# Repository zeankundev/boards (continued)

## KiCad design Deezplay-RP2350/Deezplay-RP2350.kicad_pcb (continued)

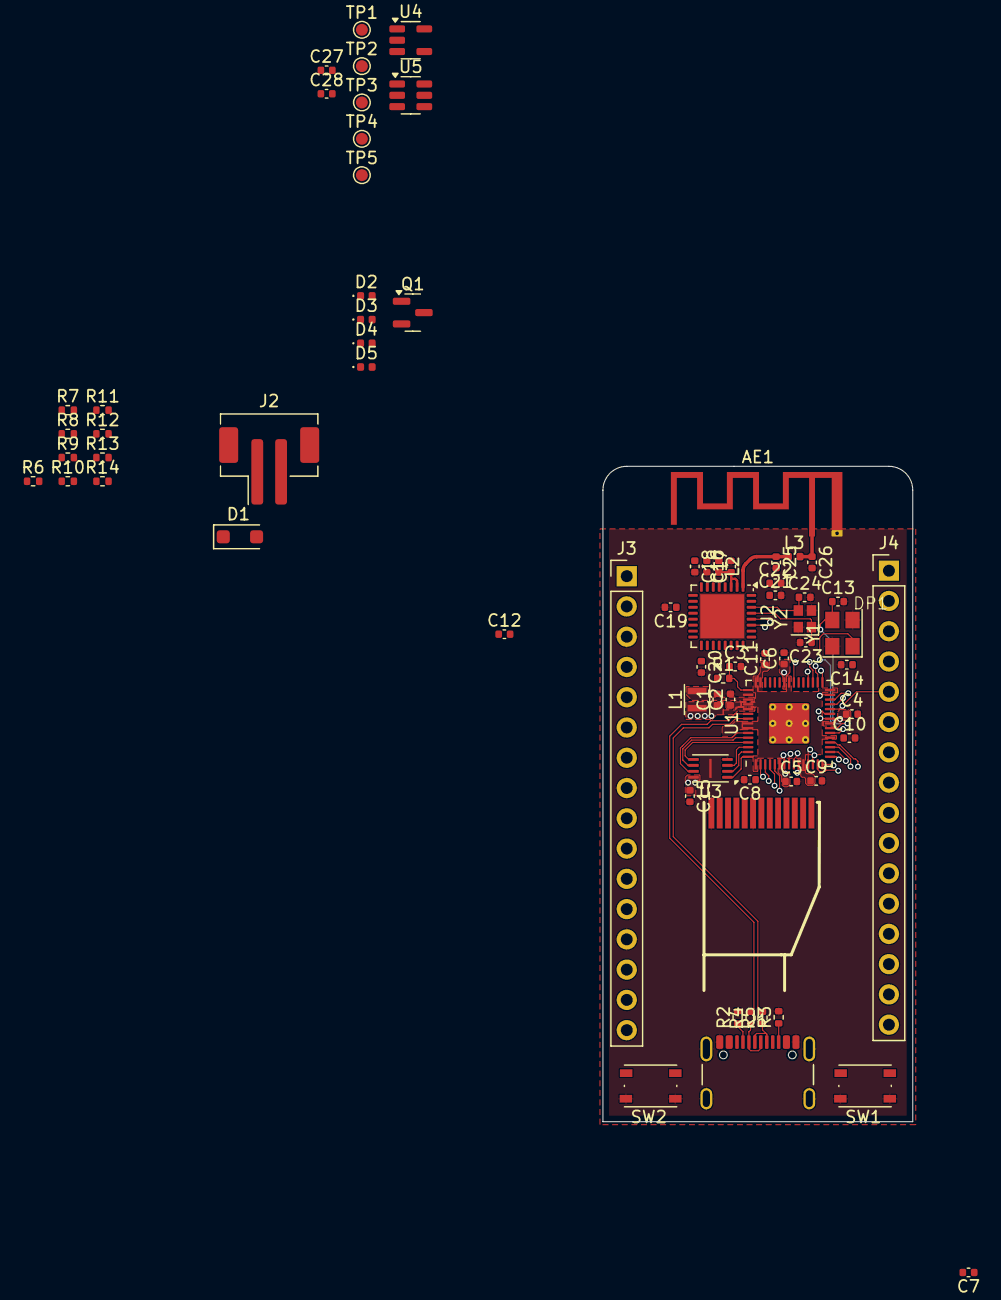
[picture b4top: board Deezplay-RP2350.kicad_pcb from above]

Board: 4 copper layers, 26.0 x 55.0 mm, 71 parts (0 on the bottom side), 72 nets.

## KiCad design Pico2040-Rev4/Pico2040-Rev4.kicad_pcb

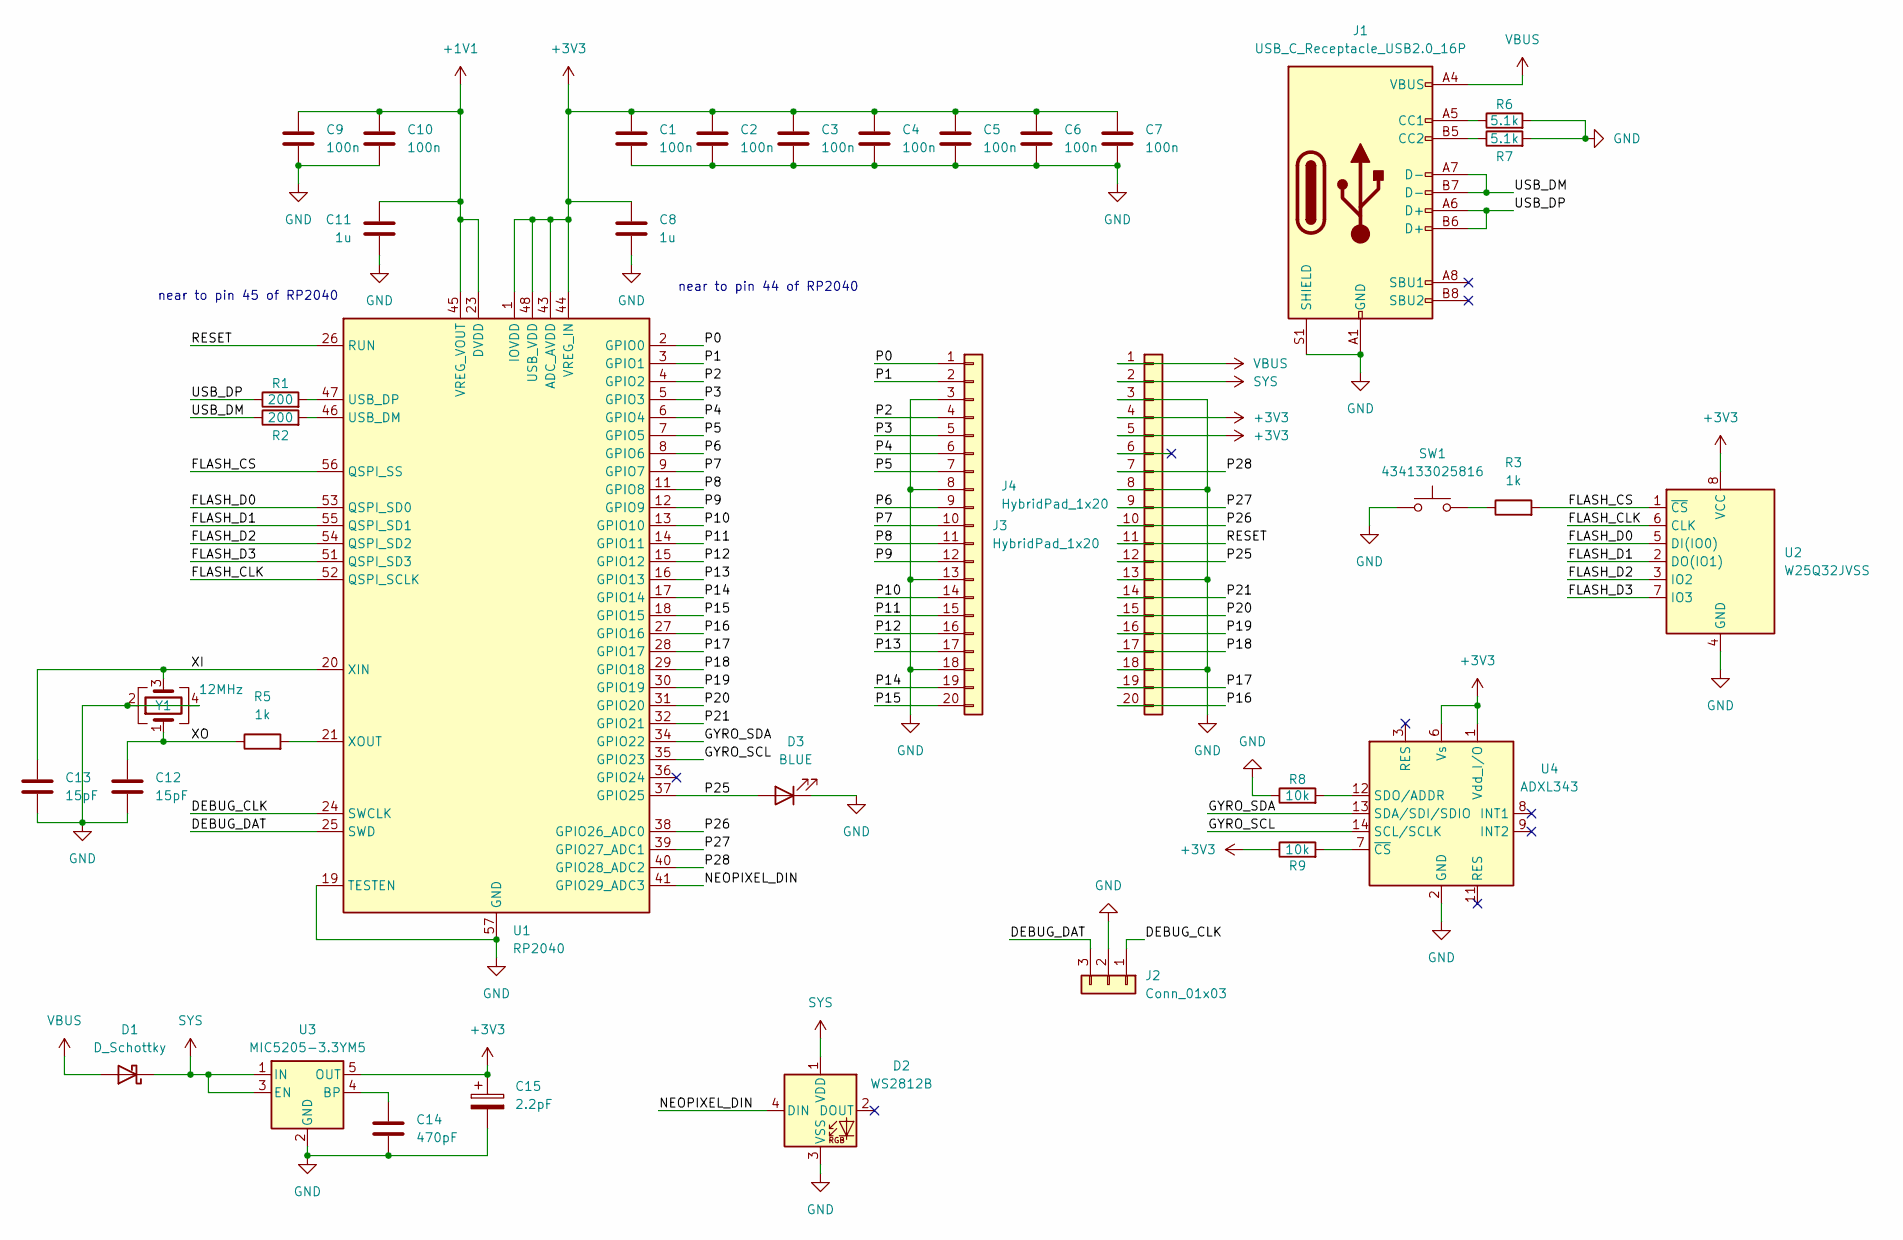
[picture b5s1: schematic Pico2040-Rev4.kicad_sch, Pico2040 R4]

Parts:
C1, C2, C3, C4, C5, C6, C7, C9, C10: 100n; C_0402_1005Metric
C8, C11: 1u; C_0402_1005Metric
C12, C13: 15pF; C_0402_1005Metric
C14: 470pF; C_0402_1005Metric
C15: 2.2pF; CP_EIA-1608-08_AVX-J
D1: D_Schottky; D_SOD-123F
D2: WS2812B; LED_WS2812B_PLCC4_5.0x5.0mm_P3.2mm
D3: BLUE; LED_0402_1005Metric
J1: USB_C_Receptacle_USB2.0_16P; USB_C_Receptacle_GCT_USB4105-xx-A_16P_TopMnt_Horizontal
J2: Conn_01x03; PinHeader_1x03_P2.54mm_Vertical
J3, J4: HybridPad_1x20; Conn_01x20_2.54mm
R1, R2: 200; R_0402_1005Metric
R3, R5: 1k; R_0402_1005Metric
R6, R7: 5.1k; R_0402_1005Metric
R8, R9: 10k; R_0402_1005Metric
SW1: 434133025816; SW_Push_1P1T_NO_Vertical_Wuerth_434133025816
U1: RP2040; QFN-56-1EP_7x7mm_P0.4mm_EP3.2x3.2mm
U2: W25Q32JVSS; 8-USON-2X3
U3: MIC5205-3.3YM5; SOT-23-5
U4: ADXL343; LGA-14_3x5mm_P0.8mm_LayoutBorder1x6y
Y1: 12MHz; Crystal_SMD_2520-4Pin_2.5x2.0mm

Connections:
+1V1: C9.1, C10.1, C11.1, U1.23 (DVDD), U1.45 (VREG_VOUT), U1.50 (DVDD)
+3V3: C1.1, C2.1, C3.1, C4.1, C5.1, C6.1, C7.1, C8.1, C15.1, J4.4, J4.5, R9.1, U1.1 (IOVDD), U1.10 (IOVDD), U1.22 (IOVDD), U1.33 (IOVDD), U1.42 (IOVDD), U1.43 (ADC_AVDD), U1.44 (VREG_IN), U1.48 (USB_VDD), U1.49 (IOVDD), U2.8 (VCC), U3.5 (OUT), U4.1 (Vdd_I/O), U4.6 (Vs)
/DEBUG_CLK: J2.1, U1.24 (SWCLK)
/DEBUG_DAT: J2.3, U1.25 (SWD)
/FLASH_CLK: U1.52 (QSPI_SCLK), U2.6 (CLK)
/FLASH_CS: R3.2, U1.56 (QSPI_SS), U2.1 (~CS)
/FLASH_D0: U1.53 (QSPI_SD0), U2.5 (DI(IO0))
/FLASH_D1: U1.55 (QSPI_SD1), U2.2 (DO(IO1))
/FLASH_D2: U1.54 (QSPI_SD2), U2.3 (IO2)
/FLASH_D3: U1.51 (QSPI_SD3), U2.7 (IO3)
/GYRO_SCL: U1.35 (GPIO23), U4.14 (SCL/SCLK)
/GYRO_SDA: U1.34 (GPIO22), U4.13 (SDA/SDI/SDIO)
/NEOPIXEL_DIN: D2.4 (DIN), U1.41 (GPIO29_ADC3)
/P0: J3.1, U1.2 (GPIO0)
/P1: J3.2, U1.3 (GPIO1)
/P2: J3.4, U1.4 (GPIO2)
/P3: J3.5, U1.5 (GPIO3)
/P4: J3.6, U1.6 (GPIO4)
/P5: J3.7, U1.7 (GPIO5)
/P6: J3.9, U1.8 (GPIO6)
/P7: J3.10, U1.9 (GPIO7)
/P8: J3.11, U1.11 (GPIO8)
/P9: J3.12, U1.12 (GPIO9)
/P10: J3.14, U1.13 (GPIO10)
/P11: J3.15, U1.14 (GPIO11)
/P12: J3.16, U1.15 (GPIO12)
/P13: J3.17, U1.16 (GPIO13)
/P14: J3.19, U1.17 (GPIO14)
/P15: J3.20, U1.18 (GPIO15)
/P16: J4.20, U1.27 (GPIO16)
/P17: J4.19, U1.28 (GPIO17)
/P18: J4.17, U1.29 (GPIO18)
/P19: J4.16, U1.30 (GPIO19)
/P20: J4.15, U1.31 (GPIO20)
/P21: J4.14, U1.32 (GPIO21)
/P25: D3.2 (A), J4.12, U1.37 (GPIO25)
/P26: J4.10, U1.38 (GPIO26_ADC0)
/P27: J4.9, U1.39 (GPIO27_ADC1)
/P28: J4.7, U1.40 (GPIO28_ADC2)
/RESET: J4.11, U1.26 (RUN)
/USB_DM: J1.A7 (D-), J1.B7 (D-), R2.1
/USB_DP: J1.A6 (D+), J1.B6 (D+), R1.1
/XI: C13.1, U1.20 (XIN), Y1.3
/XO: C12.1, R5.1, Y1.1
GND: C1.2, C2.2, C3.2, C4.2, C5.2, C6.2, C7.2, C8.2, C9.2, C10.2, C11.2, C12.2, C13.2, C14.2, C15.2, D2.3 (VSS), D3.1 (K), J1.A1 (GND), J1.A12 (GND), J1.B1 (GND), J1.B12 (GND), J1.S1 (SHIELD), J2.2, J3.3, J3.8, J3.13, J3.18, J4.3, J4.8, J4.13, J4.18, R6.2, R7.2, R8.1, SW1.1, U1.19 (TESTEN), U1.57 (GND), U2.4 (GND), U3.2 (GND), U4.2 (GND), U4.4 (GND), U4.5 (GND), Y1.2, Y1.4
unnamed: J1.A5 (CC1), R6.1
unnamed: J1.B5 (CC2), R7.1
unnamed: R3.1, SW1.2
unnamed: R2.2, U1.46 (USB_DM)
unnamed: R1.2, U1.47 (USB_DP)
unnamed: R5.2, U1.21 (XOUT)
unnamed: C14.1, U3.4 (BP)
unnamed: R8.2, U4.12 (SDO/ADDR)
unnamed: R9.2, U4.7 (~CS)
SYS: D1.1 (K), D2.1 (VDD), J4.2, U3.1 (IN), U3.3 (EN)
VBUS: D1.2 (A), J1.A4 (VBUS), J1.A9 (VBUS), J1.B4 (VBUS), J1.B9 (VBUS), J4.1

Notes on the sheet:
near to pin 44 of RP2040
near to pin 45 of RP2040

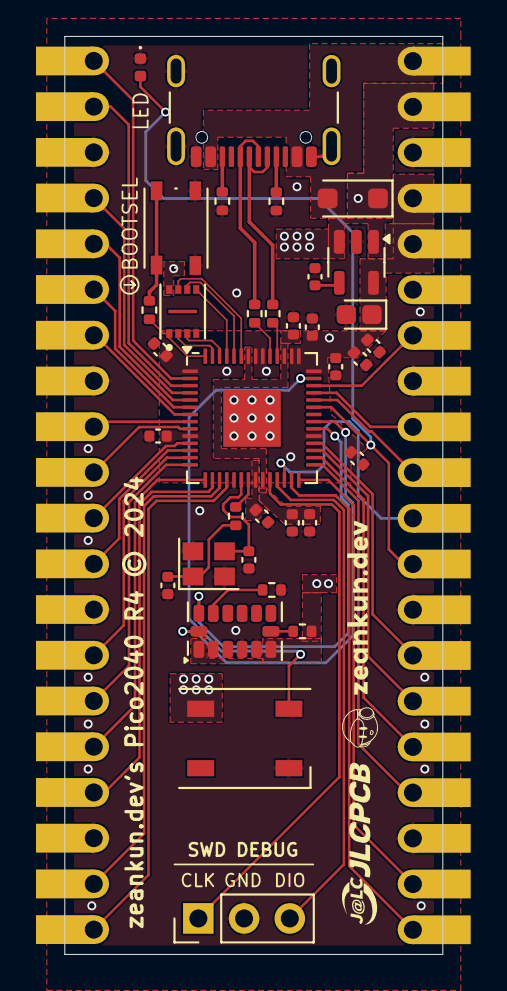
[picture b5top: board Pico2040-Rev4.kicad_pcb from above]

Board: 2 copper layers, 21.0 x 51.0 mm, 36 parts (1 on the bottom side), 56 nets.

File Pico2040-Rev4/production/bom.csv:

Designator,Footprint,Quantity,Value,LCSC Part #
"C1, C10, C2, C3, C4, C5, C6, C7, C9",0402,9,100n,
"C11, C8",0402,2,1u,
"C12, C13",0402,2,15pF,
C14,0402,1,470pF,
C15,CP_EIA-1608-08_AVX-J,1,2.2pF,
D1,D_SOD-123F,1,D_Schottky,
D2,LED_WS2812B_PLCC4_5.0x5.0mm_P3.2mm,1,WS2812B,
D3,0402,1,BLUE,
J1,USB_C_Receptacle_GCT_USB4105-xx-A_16P_TopMnt_Horizontal,1,USB_C_Receptacle_USB2.0_16P,
J2,PinHeader_1x03_P2.54mm_Vertical,1,Conn_01x03,
"R1, R2",0402,2,200,
"R3, R5",0402,2,1k,
"R6, R7",0402,2,5.1k,
"R8, R9",0402,2,10k,
SW1,SW_Push_1P1T_NO_Vertical_Wuerth_434133025816,1,434133025816,
U1,QFN-56-1EP_7x7mm_P0.4mm_EP3.2x3.2mm,1,RP2040,
U2,8-USON-2X3,1,W25Q32JVSS,
U3,SOT-23-5,1,MIC5205-3.3YM5,
U4,LGA-14_3x5mm_P0.8mm_LayoutBorder1x6y,1,ADXL343,
Y1,Crystal_SMD_2520-4Pin_2.5x2.0mm,1,12MHz,

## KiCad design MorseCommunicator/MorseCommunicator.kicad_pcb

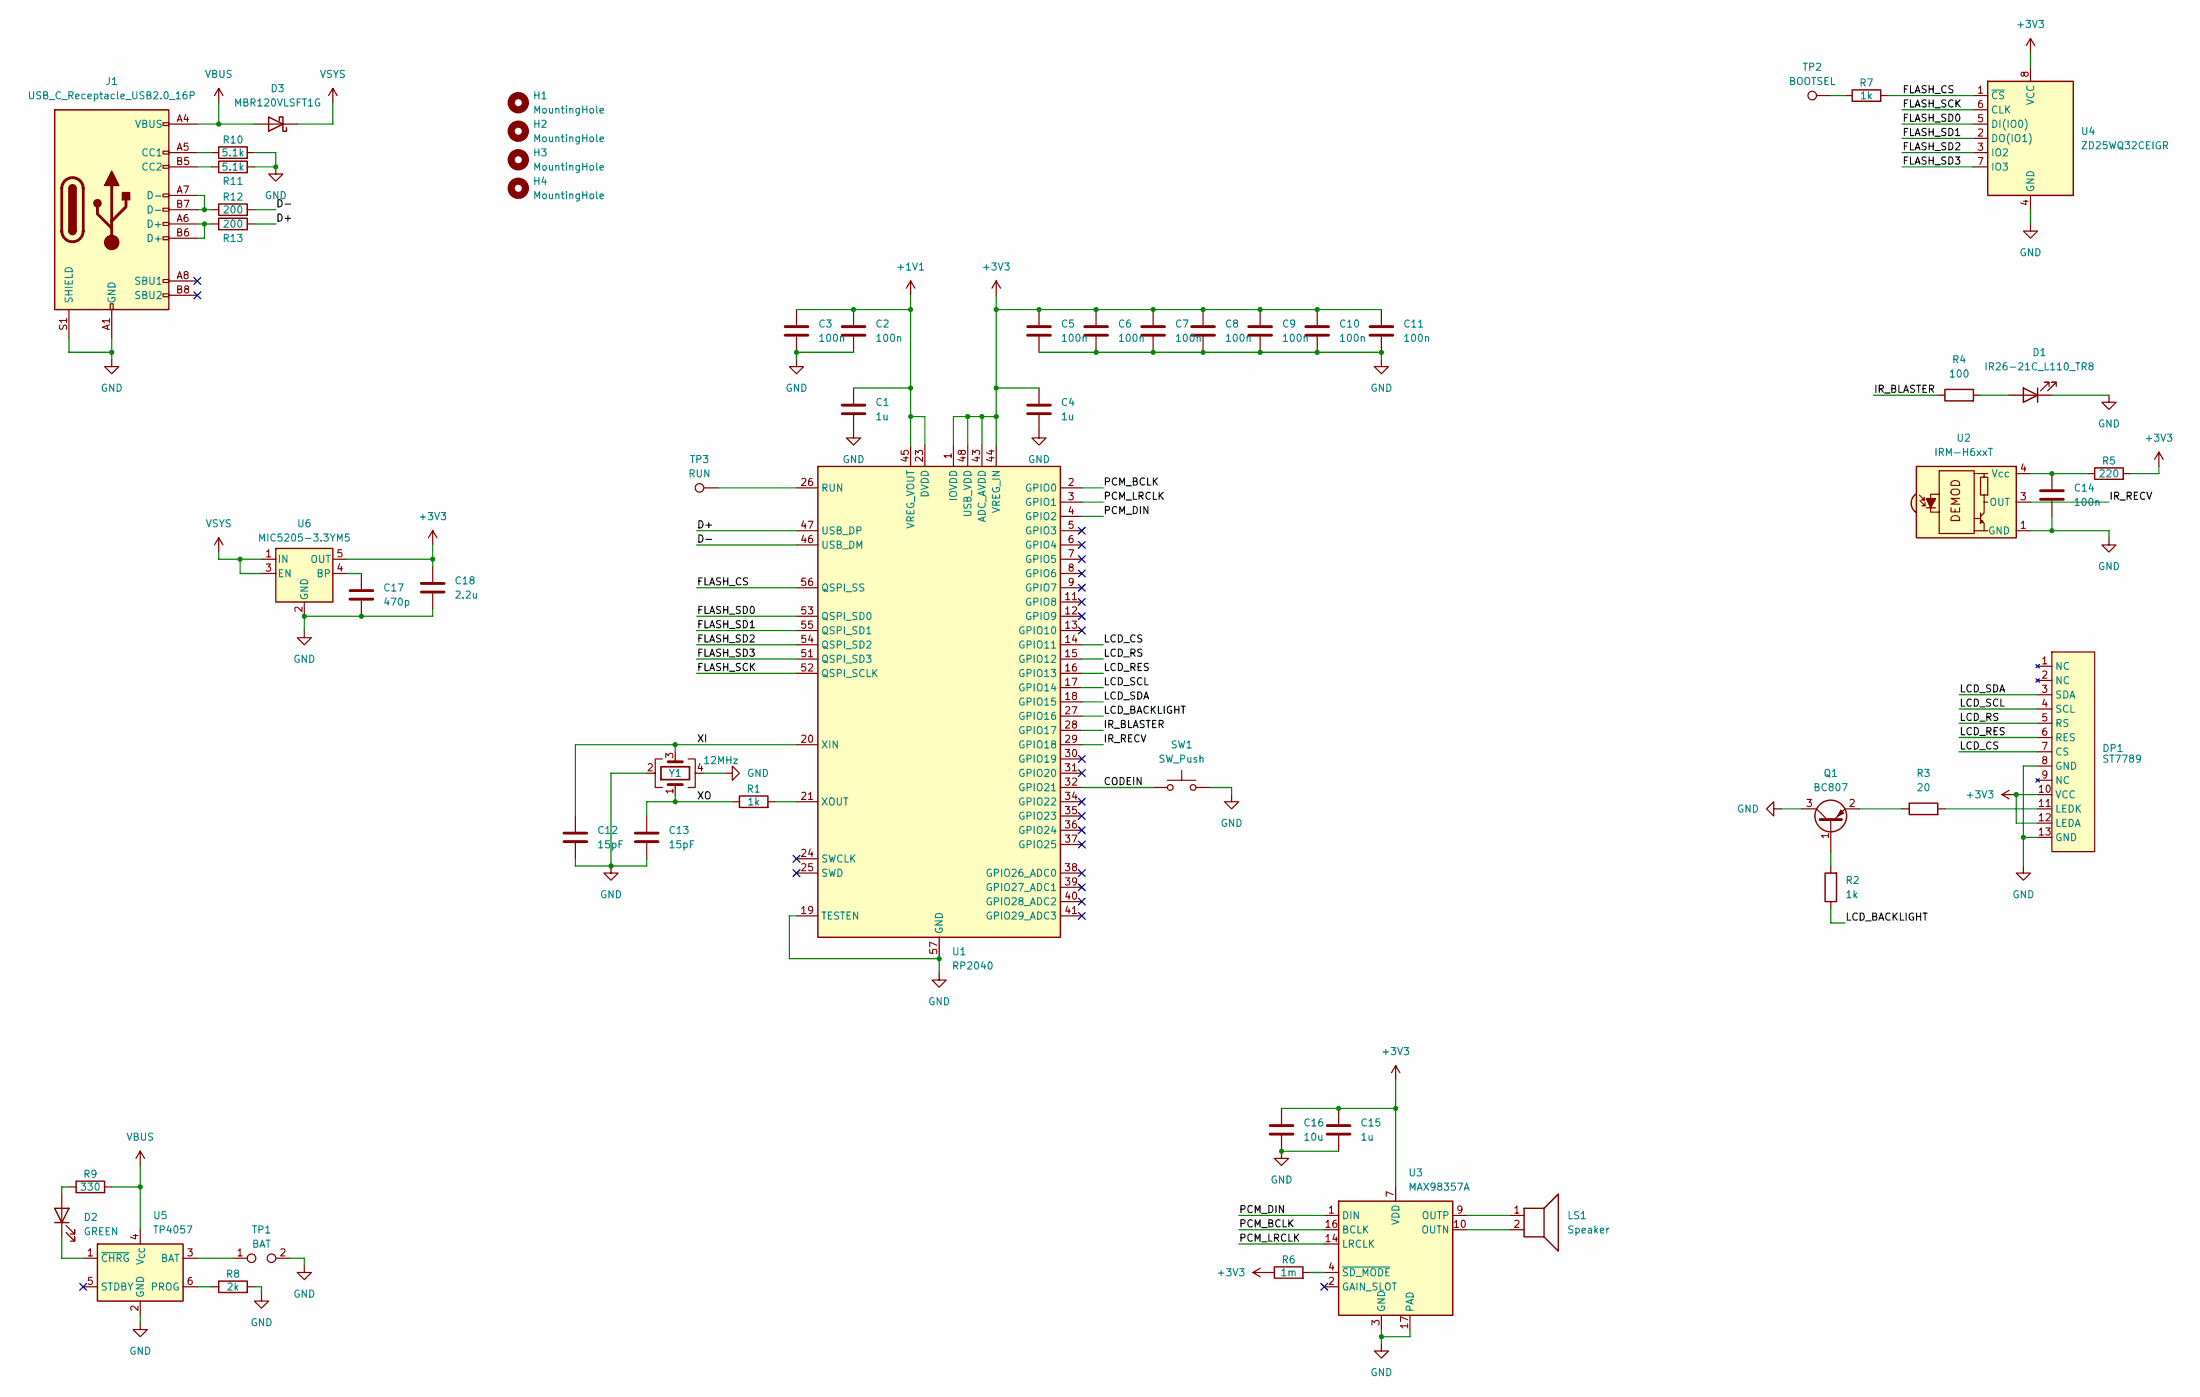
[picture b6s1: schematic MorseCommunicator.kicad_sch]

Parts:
C1, C4, C15: 1u; C_0402_1005Metric
C2, C3, C5, C6, C7, C8, C9, C10, C11, C14: 100n; C_0402_1005Metric
C12, C13: 15pF; C_0402_1005Metric
C16: 10u; C_0402_1005Metric
C17: 470p; C_0402_1005Metric
C18: 2.2u; C_0402_1005Metric
D1: IR26-21C_L110_TR8; LED_1206_3216Metric
D2: GREEN; LED_0402_1005Metric
D3: MBR120VLSFT1G; D_SOD-123F
DP1: ST7789; N114-2413THBIG01-H13
H1, H2, H3, H4: MountingHole; MountingHole_2.1mm
J1: USB_C_Receptacle_USB2.0_16P; USB_C_Receptacle_GCT_USB4105-xx-A_16P_TopMnt_Horizontal
LS1: Speaker; Speaker_13x13mm
Q1: BC807; SOT-23
R1, R2, R7: 1k; R_0402_1005Metric
R3: 20; R_0402_1005Metric
R4: 100; R_0402_1005Metric
R5: 220; R_0402_1005Metric
R6: 1m; R_0402_1005Metric
R8: 2k; R_0402_1005Metric
R9: 330; R_0402_1005Metric
R10, R11: 5.1k; R_0402_1005Metric
R12, R13: 200; R_0402_1005Metric
SW1: SW_Push; SW_SPST_Omron_B3FS-100xP
TP1: BAT; TestPoint_2Pads_Pitch2.54mm_Drill0.8mm
TP2: BOOTSEL; TestPoint_Pad_D1.0mm
TP3: RUN; TestPoint_Pad_D1.0mm
U1: RP2040; QFN-56-1EP_7x7mm_P0.4mm_EP3.2x3.2mm
U2: IRM-H6xxT; Everlight_IRM-H6xxT
U3: MAX98357A; TQFN-16-1EP_3x3mm_P0.5mm_EP1.23x1.23mm
U4: ZD25WQ32CEIGR; Winbond_USON-8-1EP_3x2mm_P0.5mm_EP0.2x1.6mm
U5: TP4057; TSOT-23-6
U6: MIC5205-3.3YM5; SOT-23-5
Y1: 12MHz; Crystal_SMD_2520-4Pin_2.5x2.0mm

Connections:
+1V1: C1.1, C2.1, C3.1, U1.23 (DVDD), U1.45 (VREG_VOUT), U1.50 (DVDD)
+3V3: C4.1, C5.1, C6.1, C7.1, C8.1, C9.1, C10.1, C11.1, C15.1, C16.1, C18.1, DP1.10 (VCC), DP1.12 (LEDA), R5.2, R6.1, U1.1 (IOVDD), U1.10 (IOVDD), U1.22 (IOVDD), U1.33 (IOVDD), U1.42 (IOVDD), U1.43 (ADC_AVDD), U1.44 (VREG_IN), U1.48 (USB_VDD), U1.49 (IOVDD), U3.7 (VDD), U3.8 (VDD), U4.8 (VCC), U6.5 (OUT)
/CODEIN: SW1.1, U1.32 (GPIO21)
/D+: R13.2, U1.47 (USB_DP)
/D-: R12.2, U1.46 (USB_DM)
/FLASH_CS: R7.2, U1.56 (QSPI_SS), U4.1 (~CS)
/FLASH_SCK: U1.52 (QSPI_SCLK), U4.6 (CLK)
/FLASH_SD0: U1.53 (QSPI_SD0), U4.5 (DI(IO0))
/FLASH_SD1: U1.55 (QSPI_SD1), U4.2 (DO(IO1))
/FLASH_SD2: U1.54 (QSPI_SD2), U4.3 (IO2)
/FLASH_SD3: U1.51 (QSPI_SD3), U4.7 (IO3)
/IR_BLASTER: R4.1, U1.28 (GPIO17)
/IR_RECV: U1.29 (GPIO18), U2.3 (OUT)
/LCD_BACKLIGHT: R2.1, U1.27 (GPIO16)
/LCD_CS: DP1.7 (CS), U1.14 (GPIO11)
/LCD_RES: DP1.6 (RES), U1.16 (GPIO13)
/LCD_RS: DP1.5 (RS), U1.15 (GPIO12)
/LCD_SCL: DP1.4 (SCL), U1.17 (GPIO14)
/LCD_SDA: DP1.3 (SDA), U1.18 (GPIO15)
/PCM_BCLK: U1.2 (GPIO0), U3.16 (BCLK)
/PCM_DIN: U1.4 (GPIO2), U3.1 (DIN)
/PCM_LRCLK: U1.3 (GPIO1), U3.14 (LRCLK)
/XI: C12.1, U1.20 (XIN), Y1.3
/XO: C13.1, R1.1, Y1.1
GND: C1.2, C2.2, C3.2, C4.2, C5.2, C6.2, C7.2, C8.2, C9.2, C10.2, C11.2, C12.2, C13.2, C14.2, C15.2, C16.2, C17.2, C18.2, D1.1 (K), DP1.8 (GND), DP1.13 (GND), J1.A1 (GND), J1.A12 (GND), J1.B1 (GND), J1.B12 (GND), J1.S1 (SHIELD), Q1.3 (C), R8.2, R10.2, R11.2, SW1.2, TP1.2, U1.19 (TESTEN), U1.57 (GND), U2.1 (GND), U2.2 (GND), U3.3 (GND), U3.11 (GND), U3.15 (GND), U3.17 (PAD), U4.4 (GND), U5.2 (GND), U6.2 (GND), Y1.2, Y1.4
unnamed: D1.2 (A), R4.2
unnamed: D2.2 (A), R9.1
unnamed: D2.1 (K), U5.1 (~CHRG)
unnamed: DP1.11 (LEDK), R3.2
unnamed: J1.A5 (CC1), R10.1
unnamed: J1.B5 (CC2), R11.1
unnamed: J1.A6 (D+), J1.B6 (D+), R13.1
unnamed: J1.A7 (D-), J1.B7 (D-), R12.1
unnamed: Q1.1 (B), R2.2
unnamed: Q1.2 (E), R3.1
unnamed: R7.1, TP2.1
unnamed: TP3.1, U1.26 (RUN)
unnamed: R1.2, U1.21 (XOUT)
unnamed: C14.1, R5.1, U2.4 (Vcc)
unnamed: LS1.2, U3.10 (OUTN)
unnamed: LS1.1, U3.9 (OUTP)
unnamed: R6.2, U3.4 (~SD_MODE)
unnamed: TP1.1, U5.3 (BAT)
unnamed: R8.1, U5.6 (PROG)
unnamed: C17.1, U6.4 (BP)
VBUS: D3.2 (A), J1.A4 (VBUS), J1.A9 (VBUS), J1.B4 (VBUS), J1.B9 (VBUS), R9.2, U5.4 (V_{CC})
VSYS: D3.1 (K), U6.1 (IN), U6.3 (EN)

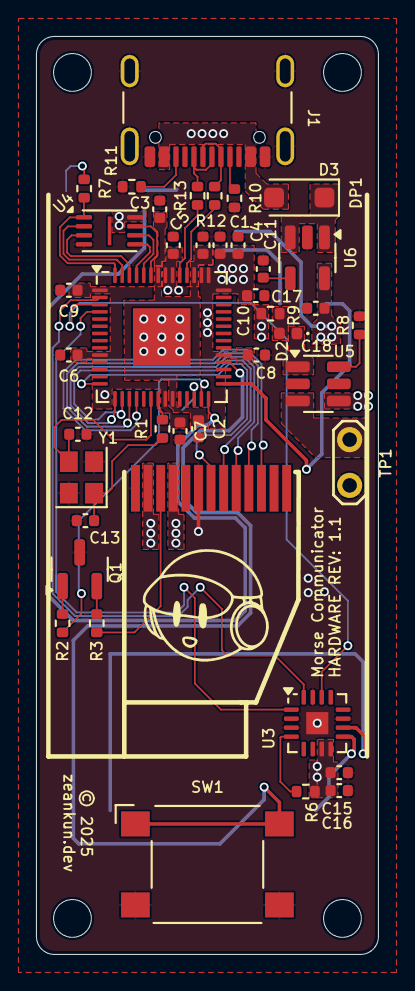
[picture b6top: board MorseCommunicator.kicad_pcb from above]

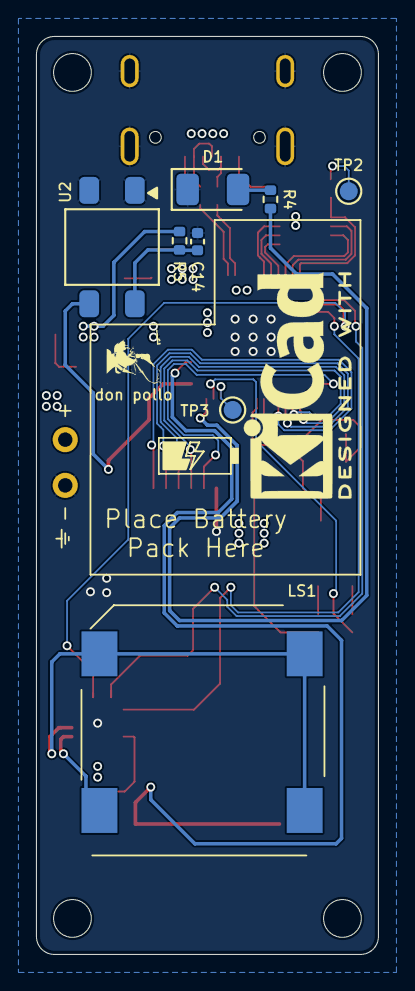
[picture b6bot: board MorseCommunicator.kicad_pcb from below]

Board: 4 copper layers, 19.0 x 51.0 mm, 53 parts (8 on the bottom side), 47 nets.

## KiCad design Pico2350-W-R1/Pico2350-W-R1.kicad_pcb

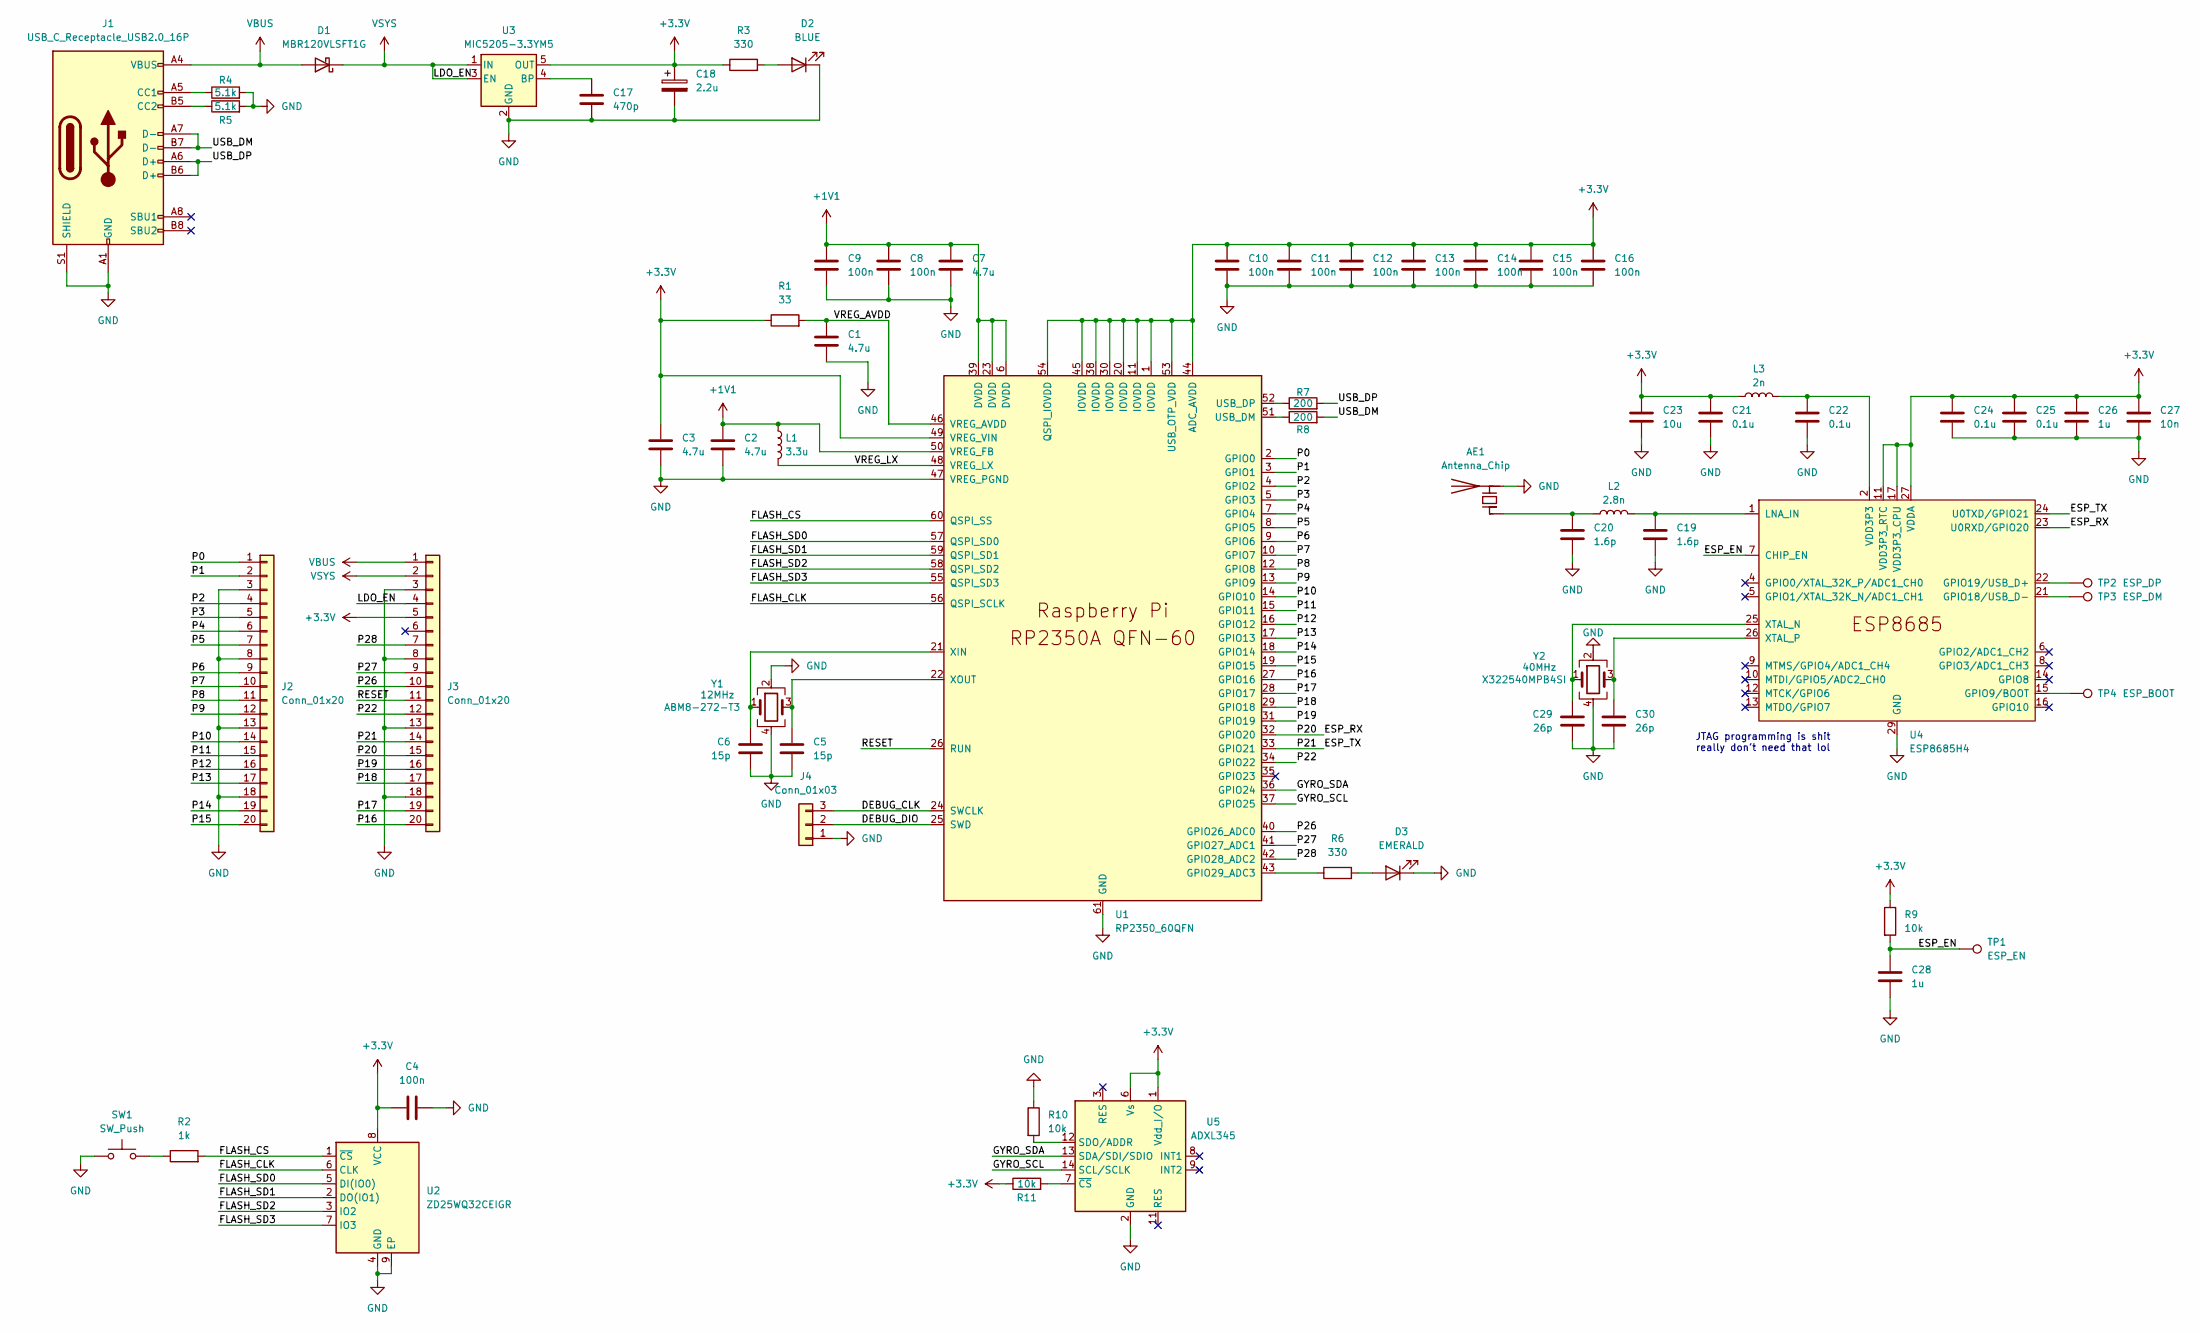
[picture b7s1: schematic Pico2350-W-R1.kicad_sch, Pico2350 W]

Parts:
AE1: Antenna_Chip; Texas_SWRA117D_2.4GHz_Left
C1, C2, C3, C7: 4.7u; C_0402_1005Metric
C4, C8, C9, C10, C11, C12, C13, C14, C15, C16: 100n; C_0402_1005Metric
C5, C6: 15p; C_0402_1005Metric
C17: 470p; C_0402_1005Metric
C18: 2.2u; CP_EIA-2012-12_Kemet-R
C19, C20: 1.6p; C_0402_1005Metric
C21, C22, C24, C25: 0.1u; C_0402_1005Metric
C23: 10u; C_0402_1005Metric
C26, C28: 1u; C_0402_1005Metric
C27: 10n; C_0402_1005Metric
C29, C30: 26p; C_0402_1005Metric
D1: MBR120VLSFT1G; D_SOD-123F
D2: BLUE; LED_0402_1005Metric
D3: EMERALD; LED_0402_1005Metric
J1: USB_C_Receptacle_USB2.0_16P; USB_C_Receptacle_GCT_USB4110
J2, J3: Conn_01x20; 1x20_2.54mm
J4: Conn_01x03; PinHeader_1x03_P2.54mm_Vertical
L1: 3.3u; L_pol_2016
L2: 2.8n; L_0402_1005Metric
L3: 2n; L_0402_1005Metric
R1: 33; R_0402_1005Metric
R2: 1k; R_0402_1005Metric
R3, R6: 330; R_0402_1005Metric
R4, R5: 5.1k; R_0402_1005Metric
R7, R8: 200; R_0402_1005Metric
R9, R10, R11: 10k; R_0402_1005Metric
SW1: SW_Push; SW_Push_1P1T_NO_Vertical_Wuerth_434133025816
TP1: ESP_EN; TestPoint_Pad_D1.0mm
TP2: ESP_DP; TestPoint_Pad_D1.0mm
TP3: ESP_DM; TestPoint_Pad_D1.0mm
TP4: ESP_BOOT; TestPoint_Pad_D1.0mm
U1: RP2350_60QFN; RP2350-QFN-60-1EP_7x7_P0.4mm_EP3.4x3.4mm_ThermalVias
U2: ZD25WQ32CEIGR; 8-USON-2X3
U3: MIC5205-3.3YM5; SOT-23-5
U4: ESP8685H4; QFN-28-1EP_4x4mm_P0.4mm_EP2.6x2.6mm
U5: ADXL345; LGA-14_3x5mm_P0.8mm_LayoutBorder1x6y
Y1: 12MHz; Crystal_SMD_3225-4Pin_3.2x2.5mm
Y2: 40MHz; Crystal_SMD_3225-4Pin_3.2x2.5mm

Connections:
+1V1: C2.1, C7.1, C8.1, C9.1, L1.1, U1.6 (DVDD), U1.23 (DVDD), U1.39 (DVDD), U1.50 (VREG_FB)
+3.3V: C3.1, C4.1, C10.1, C11.1, C12.1, C13.1, C14.1, C15.1, C16.1, C18.1, C21.1, C23.1, C24.1, C25.1, C26.1, C27.1, J3.5, L3.1, R1.1, R3.1, R9.1, R11.1, U1.1 (IOVDD), U1.11 (IOVDD), U1.20 (IOVDD), U1.30 (IOVDD), U1.38 (IOVDD), U1.44 (ADC_AVDD), U1.45 (IOVDD), U1.49 (VREG_VIN), U1.53 (USB_OTP_VDD), U1.54 (QSPI_IOVDD), U2.8 (VCC), U3.5 (OUT), U4.11 (VDD3P3_RTC), U4.17 (VDD3P3_CPU), U4.27 (VDDA), U4.28 (VDDA), U5.1 (Vdd_I/O), U5.6 (Vs)
/DEBUG_CLK: J4.3, U1.24 (SWCLK)
/DEBUG_DIO: J4.2, U1.25 (SWD)
/ESP_EN: C28.1, R9.2, TP1.1, U4.7 (CHIP_EN)
/ESP_RX: J3.15, U1.32 (GPIO20), U4.23 (U0RXD/GPIO20)
/ESP_TX: J3.14, U1.33 (GPIO21), U4.24 (U0TXD/GPIO21)
/FLASH_CLK: U1.56 (QSPI_SCLK), U2.6 (CLK)
/FLASH_CS: R2.2, U1.60 (QSPI_SS), U2.1 (~CS)
/FLASH_SD0: U1.57 (QSPI_SD0), U2.5 (DI(IO0))
/FLASH_SD1: U1.59 (QSPI_SD1), U2.2 (DO(IO1))
/FLASH_SD2: U1.58 (QSPI_SD2), U2.3 (IO2)
/FLASH_SD3: U1.55 (QSPI_SD3), U2.7 (IO3)
/GYRO_SCL: U1.37 (GPIO25), U5.14 (SCL/SCLK)
/GYRO_SDA: U1.36 (GPIO24), U5.13 (SDA/SDI/SDIO)
/P0: J2.1, U1.2 (GPIO0)
/P1: J2.2, U1.3 (GPIO1)
/P2: J2.4, U1.4 (GPIO2)
/P3: J2.5, U1.5 (GPIO3)
/P4: J2.6, U1.7 (GPIO4)
/P5: J2.7, U1.8 (GPIO5)
/P6: J2.9, U1.9 (GPIO6)
/P7: J2.10, U1.10 (GPIO7)
/P8: J2.11, U1.12 (GPIO8)
/P9: J2.12, U1.13 (GPIO9)
/P10: J2.14, U1.14 (GPIO10)
/P11: J2.15, U1.15 (GPIO11)
/P12: J2.16, U1.16 (GPIO12)
/P13: J2.17, U1.17 (GPIO13)
/P14: J2.19, U1.18 (GPIO14)
/P15: J2.20, U1.19 (GPIO15)
/P16: J3.20, U1.27 (GPIO16)
/P17: J3.19, U1.28 (GPIO17)
/P18: J3.17, U1.29 (GPIO18)
/P19: J3.16, U1.31 (GPIO19)
/P22: J3.12, U1.34 (GPIO22)
/P26: J3.10, U1.40 (GPIO26_ADC0)
/P27: J3.9, U1.41 (GPIO27_ADC1)
/P28: J3.7, U1.42 (GPIO28_ADC2)
/RESET: J3.11, U1.26 (RUN)
/USB_DM: J1.A7 (D-), J1.B7 (D-), R8.2
/USB_DP: J1.A6 (D+), J1.B6 (D+), R7.2
/VREG_AVDD: C1.1, R1.2, U1.46 (VREG_AVDD)
/VREG_LX: L1.2, U1.48 (VREG_LX)
GND: AE1.2 (PCB_Trace), C1.2, C2.2, C3.2, C4.2, C5.2, C6.2, C7.2, C8.2, C9.2, C10.2, C11.2, C12.2, C13.2, C14.2, C15.2, C16.2, C17.2, C18.2, C19.2, C20.2, C21.2, C22.2, C23.2, C24.2, C25.2, C26.2, C27.2, C28.2, C29.2, C30.2, D2.1 (K), D3.1 (K), J1.A1 (GND), J1.A12 (GND), J1.B1 (GND), J1.B12 (GND), J1.S1 (SHIELD), J2.3, J2.8, J2.13, J2.18, J3.3, J3.8, J3.13, J3.18, J4.1, R4.2, R5.2, R10.1, SW1.1, U1.47 (VREG_PGND), U1.61 (GND), U2.4 (GND), U2.9 (EP), U3.2 (GND), U4.29 (GND), U5.2 (GND), U5.4 (GND), U5.5 (GND), Y1.2, Y1.4, Y2.2, Y2.4
unnamed: AE1.1 (FEED), C20.1, L2.1
unnamed: C22.1, L3.2, U4.2 (VDD3P3), U4.3 (VDD3P3)
unnamed: D2.2 (A), R3.2
unnamed: D3.2 (A), R6.2
unnamed: J1.A5 (CC1), R4.1
unnamed: J1.B5 (CC2), R5.1
unnamed: R2.1, SW1.2
unnamed: R6.1, U1.43 (GPIO29_ADC3)
unnamed: R8.1, U1.51 (USB_DM)
unnamed: R7.1, U1.52 (USB_DP)
unnamed: C6.1, U1.21 (XIN), Y1.1
unnamed: C5.1, U1.22 (XOUT), Y1.3
unnamed: C17.1, U3.4 (BP)
unnamed: TP4.1, U4.15 (GPIO9/BOOT)
unnamed: TP3.1, U4.21 (GPIO18/USB_D-)
unnamed: TP2.1, U4.22 (GPIO19/USB_D+)
unnamed: C19.1, L2.2, U4.1 (LNA_IN)
unnamed: C29.1, U4.25 (XTAL_N), Y2.1
unnamed: C30.1, U4.26 (XTAL_P), Y2.3
unnamed: R10.2, U5.12 (SDO/ADDR)
unnamed: R11.2, U5.7 (~CS)
VBUS: D1.2 (A), J1.A4 (VBUS), J1.A9 (VBUS), J1.B4 (VBUS), J1.B9 (VBUS), J3.1
VSYS: D1.1 (K), J3.2, J3.4, U3.1 (IN), U3.3 (EN)

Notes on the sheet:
JTAG programming is shit really don't need that lol

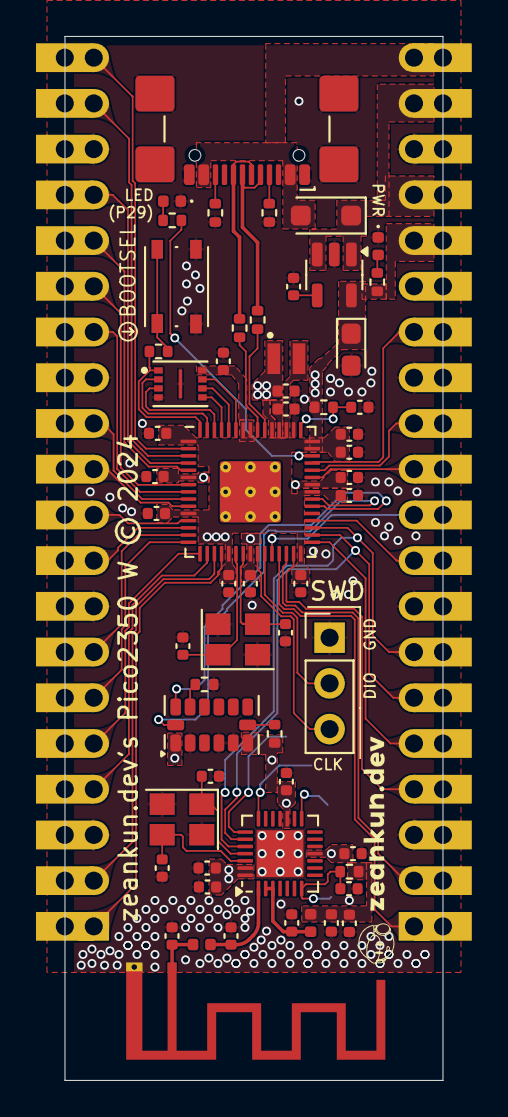
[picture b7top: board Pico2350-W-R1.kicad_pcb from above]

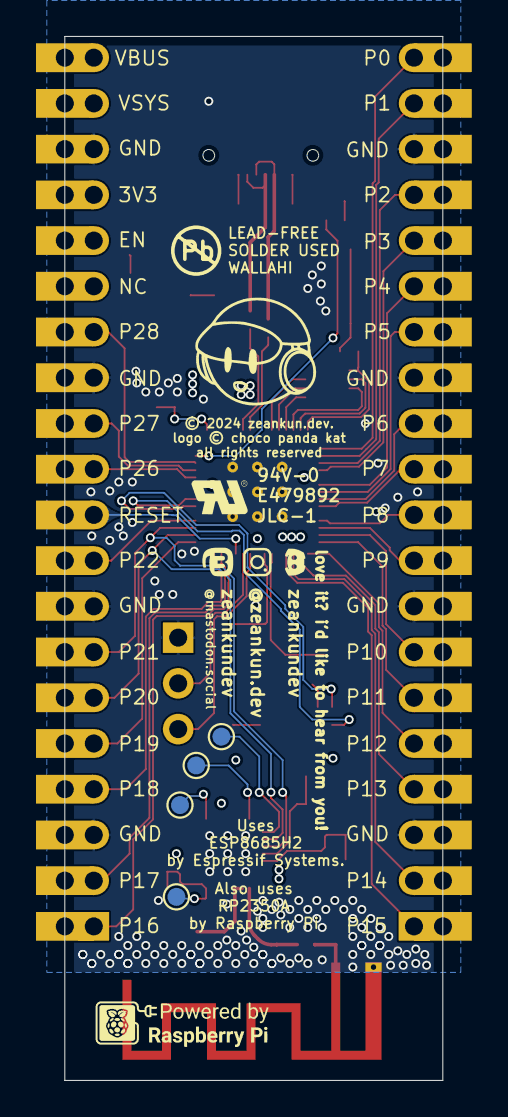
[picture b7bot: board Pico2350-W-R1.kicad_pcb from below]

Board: 4 copper layers, 21.0 x 58.0 mm, 64 parts (5 on the bottom side), 68 nets.
